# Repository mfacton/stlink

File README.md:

# Minified STLink V2 Clone

## Usage
Flash the unprotecter bootloader
Use the updater stlink software for initial update
Update stlink with regular software

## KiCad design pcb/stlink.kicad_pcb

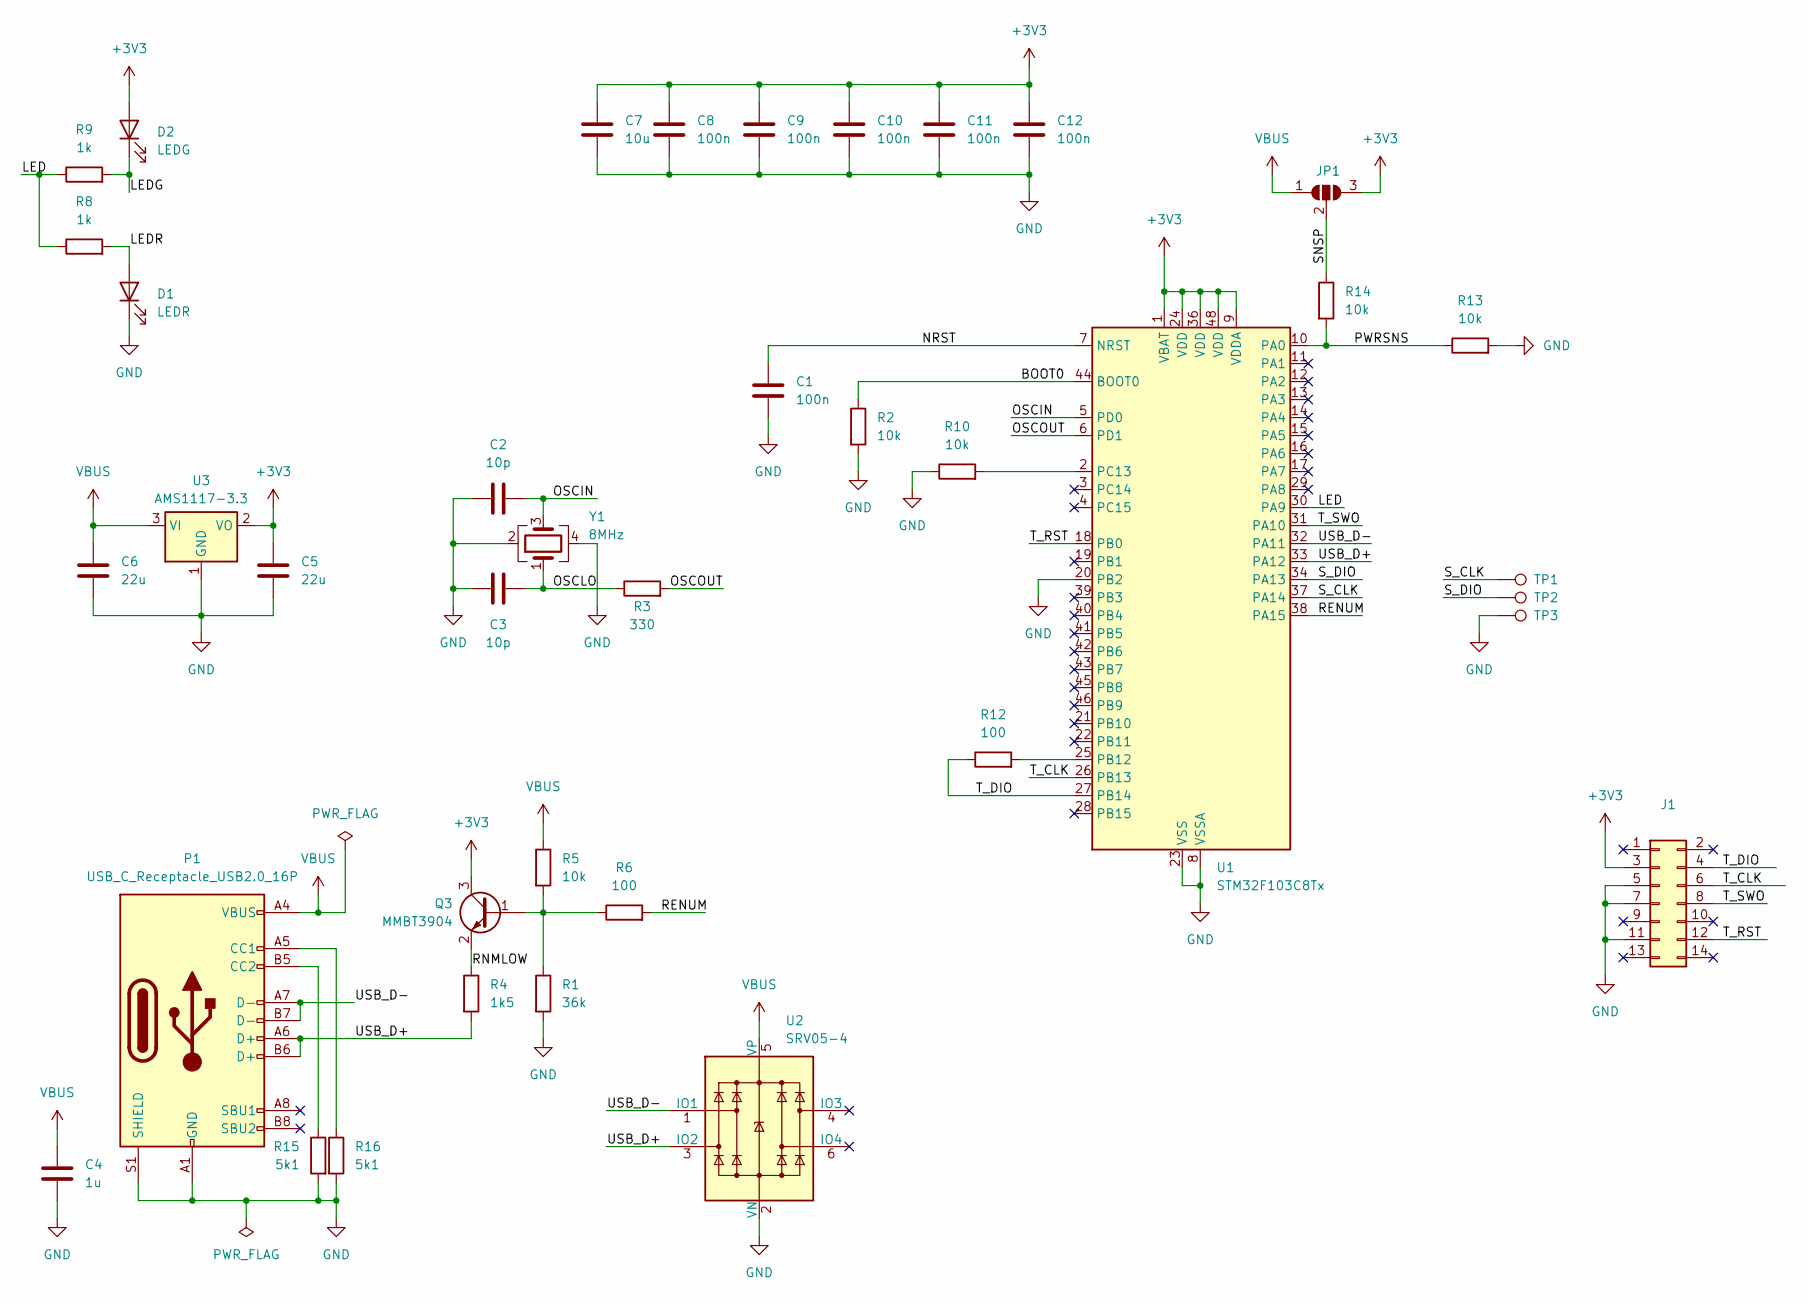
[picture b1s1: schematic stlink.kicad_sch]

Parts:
C1, C8, C9, C10, C11, C12: 100n; C_0402_1005Metric
C2, C3: 10p; C_0402_1005Metric
C4: 1u; C_0402_1005Metric
C5: 22u; C_0603_1608Metric
C6: 22u; C_0805_2012Metric
C7: 10u; C_0402_1005Metric
D1: LEDR; LED_0603_1608Metric; LCSC C2286
D2: LEDG; LED_0603_1608Metric; LCSC C2986059
J1: Conn_02x07_Odd_Even; PinHeader_2x07_P1.27mm_Vertical; LCSC C2881789
JP1: SolderJumper_3_Open; SolderJumper-3_P1.3mm_Open_RoundedPad1.0x1.5mm
P1: USB_C_Receptacle_USB2.0_16P; USB_C_Receptacle_GCT_USB4105-xx-A_16P_TopMnt_Horizontal; MPN C165948
Q3: MMBT3904; SOT-23
R1: 36k; R_0402_1005Metric
R2, R5, R10, R13, R14: 10k; R_0402_1005Metric
R3: 330; R_0402_1005Metric
R4: 1k5; R_0402_1005Metric
R6, R12: 100; R_0402_1005Metric
R8, R9: 1k; R_0402_1005Metric
R15, R16: 5k1; R_0402_1005Metric; LCSC C25905
TP1, TP2, TP3: TestPoint; TestPoint_Pad_D1.0mm
U1: STM32F103C8Tx; LQFP-48_7x7mm_P0.5mm; LCSC C8734
U2: SRV05-4; SOT-23-6; LCSC C7420376
U3: AMS1117-3.3; SOT-223-3_TabPin2
Y1: 8MHz; Crystal_SMD_3225-4Pin_3.2x2.5mm; LCSC C400090

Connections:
+3V3: C5.1, C7.1, C8.1, C9.1, C10.1, C11.1, C12.1, D2.2 (A), J1.3, JP1.3 (B), Q3.3 (C), U1.1 (VBAT), U1.9 (VDDA), U1.24 (VDD), U1.36 (VDD), U1.48 (VDD), U3.2 (VO)
/BOOT0: R2.1, U1.44 (BOOT0)
/LED: R8.1, R9.1, U1.30 (PA9)
/LEDG: D2.1 (K), R9.2
/LEDR: D1.2 (A), R8.2
/NRST: C1.1, U1.7 (NRST)
/OSCIN: C2.2, U1.5 (PD0), Y1.3
/OSCLO: C3.2, R3.1, Y1.1
/OSCOUT: R3.2, U1.6 (PD1)
/PWRSNS: R13.1, R14.2, U1.10 (PA0)
/RENUM: R6.2, U1.38 (PA15)
/RNMLOW: Q3.2 (E), R4.1
/SNSP: JP1.2 (C), R14.1
/S_CLK: TP1.1, U1.37 (PA14)
/S_DIO: TP2.1, U1.34 (PA13)
/T_CLK: J1.6, U1.26 (PB13)
/T_DIO: J1.4, R12.1, U1.27 (PB14)
/T_RST: J1.12, U1.18 (PB0)
/T_SWO: J1.8, U1.31 (PA10)
/USB_D+: P1.A6 (D+), P1.B6 (D+), R4.2, U1.33 (PA12), U2.3 (IO2)
/USB_D-: P1.A7 (D-), P1.B7 (D-), U1.32 (PA11), U2.1 (IO1)
GND: C1.2, C2.1, C3.1, C4.2, C5.2, C6.2, C7.2, C8.2, C9.2, C10.2, C11.2, C12.2, D1.1 (K), J1.5, J1.7, J1.11, P1.A1 (GND), P1.A12 (GND), P1.B1 (GND), P1.B12 (GND), P1.S1 (SHIELD), R1.2, R2.2, R10.1, R13.2, R15.2, R16.2, TP3.1, U1.8 (VSSA), U1.20 (PB2), U1.23 (VSS), U1.35 (VSS), U1.47 (VSS), U2.2 (VN), U3.1 (GND), Y1.2, Y1.4
unnamed: P1.A5 (CC1), R16.1
unnamed: P1.B5 (CC2), R15.1
unnamed: Q3.1 (B), R1.1, R5.2, R6.1
unnamed: R12.2, U1.25 (PB12)
unnamed: R10.2, U1.2 (PC13)
VBUS: C4.1, C6.1, JP1.1 (A), P1.A4 (VBUS), P1.A9 (VBUS), P1.B4 (VBUS), P1.B9 (VBUS), R5.1, U2.5 (VP), U3.3 (VI)

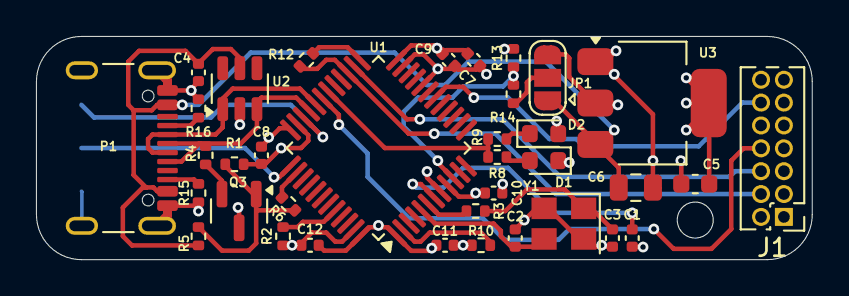
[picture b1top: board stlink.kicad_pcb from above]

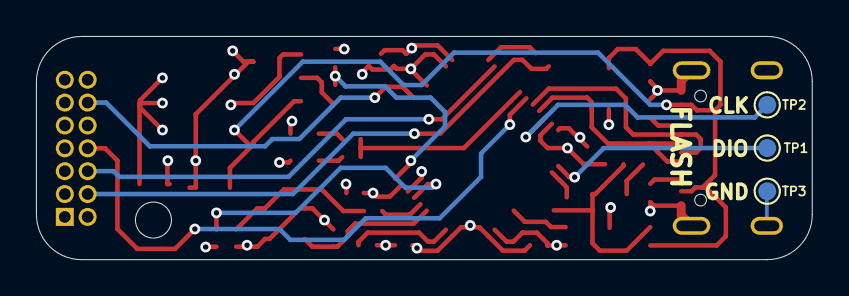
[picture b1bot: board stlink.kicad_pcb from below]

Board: 4 copper layers, 43.1 x 12.4 mm, 39 parts (3 on the bottom side), 28 nets.

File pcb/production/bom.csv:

Designator,Footprint,Quantity,Value,LCSC Part #
"C1, C10, C11, C12, C8, C9",0402,6,100n,
"C2, C3",0402,2,10p,
C4,0402,1,1u,
C5,0603,1,22u,
C6,0805,1,22u,
C7,0402,1,10u,
D1,0603,1,LEDR,C2286
D2,0603,1,LEDG,C2986059
J1,PinHeader_2x07_P1.27mm_Vertical,1,Conn_02x07_Odd_Even,C2881789
P1,USB_C_Receptacle_GCT_USB4105-xx-A_16P_TopMnt_Horizontal,1,USB_C_Receptacle_USB2.0_16P,C165948
Q3,SOT-23,1,MMBT3904,
R1,0402,1,36k,
"R10, R13, R14, R2, R5",0402,5,10k,
"R12, R6",0402,2,100,
"R15, R16",0402,2,5k1,C25905
R3,0402,1,330,
R4,0402,1,1k5,
"R8, R9",0402,2,1k,
U1,LQFP-48_7x7mm_P0.5mm,1,STM32F103C8Tx,C8734
U2,SOT-23-6,1,SRV05-4,C7420376
U3,SOT-223-3_TabPin2,1,AMS1117-3.3,
Y1,Crystal_SMD_3225-4Pin_3.2x2.5mm,1,16MHz,

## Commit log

2024-05-13 Add gitignore
2024-05-13 Fix readme title
2024-05-13 Transfer project
2024-05-13 Add bin file
2024-05-13 Add old updater
2024-05-13 Add instructions
2024-06-06 Remove OS garbage
2024-06-06 Remove pcb lck files
2024-06-06 Re-add ignored files
2024-10-16 Add image
2024-12-13 Save
